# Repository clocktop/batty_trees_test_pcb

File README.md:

# batty_trees_test_pcb
KiCAD project for testing the Batty Trees TSMC June 2020 Tapeout

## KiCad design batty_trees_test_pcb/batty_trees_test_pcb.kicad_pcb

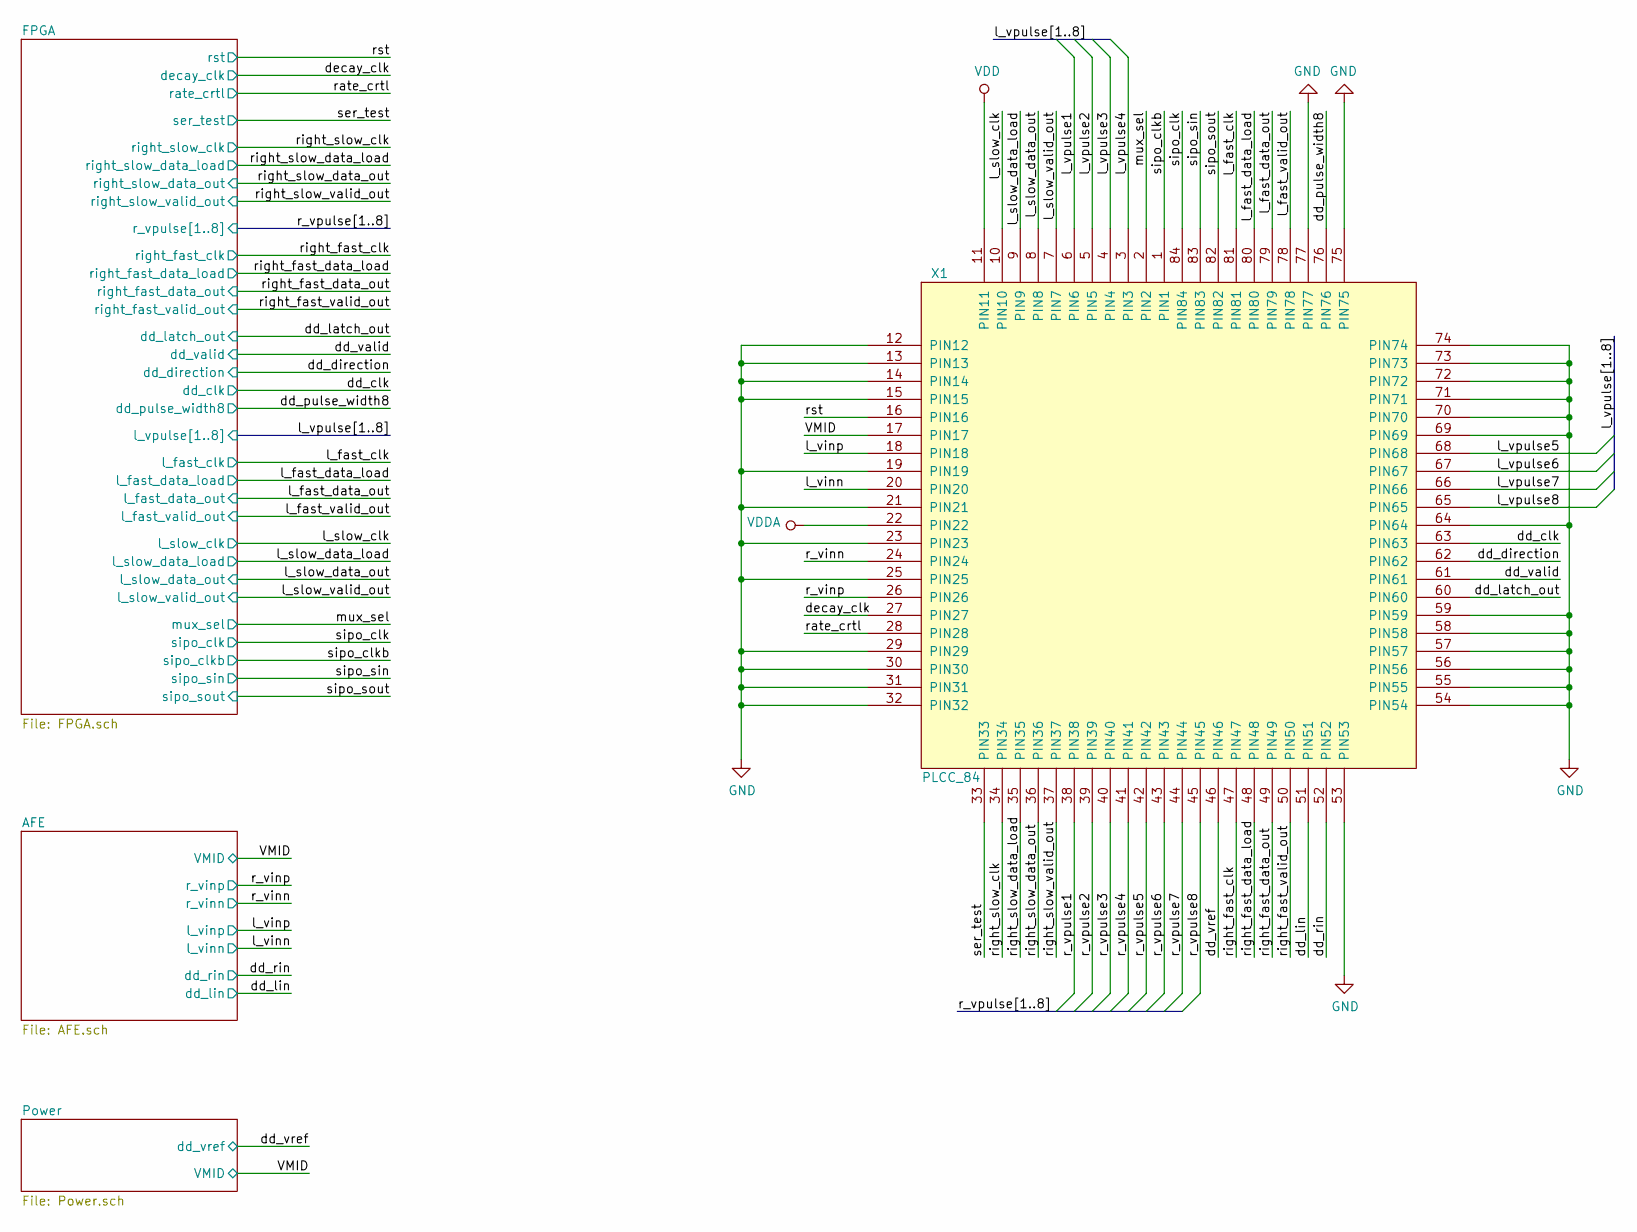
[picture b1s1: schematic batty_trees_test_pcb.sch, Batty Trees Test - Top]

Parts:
X1: PLCC_84; PLCC_84POS

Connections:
/VMID: X1.17 (PIN17); also elsewhere on the board
/dd_clk: X1.63 (PIN63); also elsewhere on the board
/dd_direction: X1.62 (PIN62); also elsewhere on the board
/dd_latch_out: X1.60 (PIN60); also elsewhere on the board
/dd_lin: X1.51 (PIN51); also elsewhere on the board
/dd_pulse_width8: X1.76 (PIN76); also elsewhere on the board
/dd_rin: X1.52 (PIN52); also elsewhere on the board
/dd_valid: X1.61 (PIN61); also elsewhere on the board
/dd_vref: X1.46 (PIN46); also elsewhere on the board
/decay_clk: X1.27 (PIN27); also elsewhere on the board
/l_fast_clk: X1.81 (PIN81); also elsewhere on the board
/l_fast_data_load: X1.80 (PIN80); also elsewhere on the board
/l_fast_data_out: X1.79 (PIN79); also elsewhere on the board
/l_fast_valid_out: X1.78 (PIN78); also elsewhere on the board
/l_slow_clk: X1.10 (PIN10); also elsewhere on the board
/l_slow_data_load: X1.9 (PIN9); also elsewhere on the board
/l_slow_data_out: X1.8 (PIN8); also elsewhere on the board
/l_slow_valid_out: X1.7 (PIN7); also elsewhere on the board
/l_vinn: X1.20 (PIN20); also elsewhere on the board
/l_vinp: X1.18 (PIN18); also elsewhere on the board
/l_vpulse1: X1.6 (PIN6); also elsewhere on the board
/l_vpulse2: X1.5 (PIN5); also elsewhere on the board
/l_vpulse3: X1.4 (PIN4); also elsewhere on the board
/l_vpulse4: X1.3 (PIN3); also elsewhere on the board
/l_vpulse5: X1.68 (PIN68); also elsewhere on the board
/l_vpulse6: X1.67 (PIN67); also elsewhere on the board
/l_vpulse7: X1.66 (PIN66); also elsewhere on the board
/l_vpulse8: X1.65 (PIN65); also elsewhere on the board
/mux_sel: X1.2 (PIN2); also elsewhere on the board
/r_vinn: X1.24 (PIN24); also elsewhere on the board
/r_vinp: X1.26 (PIN26); also elsewhere on the board
/r_vpulse1: X1.38 (PIN38); also elsewhere on the board
/r_vpulse2: X1.39 (PIN39); also elsewhere on the board
/r_vpulse3: X1.40 (PIN40); also elsewhere on the board
/r_vpulse4: X1.41 (PIN41); also elsewhere on the board
/r_vpulse5: X1.42 (PIN42); also elsewhere on the board
/r_vpulse6: X1.43 (PIN43); also elsewhere on the board
/r_vpulse7: X1.44 (PIN44); also elsewhere on the board
/r_vpulse8: X1.45 (PIN45); also elsewhere on the board
/rate_crtl: X1.28 (PIN28); also elsewhere on the board
/right_fast_clk: X1.47 (PIN47); also elsewhere on the board
/right_fast_data_load: X1.48 (PIN48); also elsewhere on the board
/right_fast_data_out: X1.49 (PIN49); also elsewhere on the board
/right_fast_valid_out: X1.50 (PIN50); also elsewhere on the board
/right_slow_clk: X1.34 (PIN34); also elsewhere on the board
/right_slow_data_load: X1.35 (PIN35); also elsewhere on the board
/right_slow_data_out: X1.36 (PIN36); also elsewhere on the board
/right_slow_valid_out: X1.37 (PIN37); also elsewhere on the board
/rst: X1.16 (PIN16); also elsewhere on the board
/ser_test: X1.33 (PIN33); also elsewhere on the board
/sipo_clk: X1.84 (PIN84); also elsewhere on the board
/sipo_clkb: X1.1 (PIN1); also elsewhere on the board
/sipo_sin: X1.83 (PIN83); also elsewhere on the board
/sipo_sout: X1.82 (PIN82); also elsewhere on the board
GND: X1.12 (PIN12), X1.13 (PIN13), X1.14 (PIN14), X1.15 (PIN15), X1.19 (PIN19), X1.21 (PIN21), X1.23 (PIN23), X1.25 (PIN25), X1.29 (PIN29), X1.30 (PIN30), X1.31 (PIN31), X1.32 (PIN32), X1.53 (PIN53), X1.54 (PIN54), X1.55 (PIN55), X1.56 (PIN56), X1.57 (PIN57), X1.58 (PIN58), X1.59 (PIN59), X1.64 (PIN64), X1.69 (PIN69), X1.70 (PIN70), X1.71 (PIN71), X1.72 (PIN72), X1.73 (PIN73), X1.74 (PIN74), X1.75 (PIN75), X1.77 (PIN77); also elsewhere on the board
VDD: X1.11 (PIN11); also elsewhere on the board
VDDA: X1.22 (PIN22); also elsewhere on the board

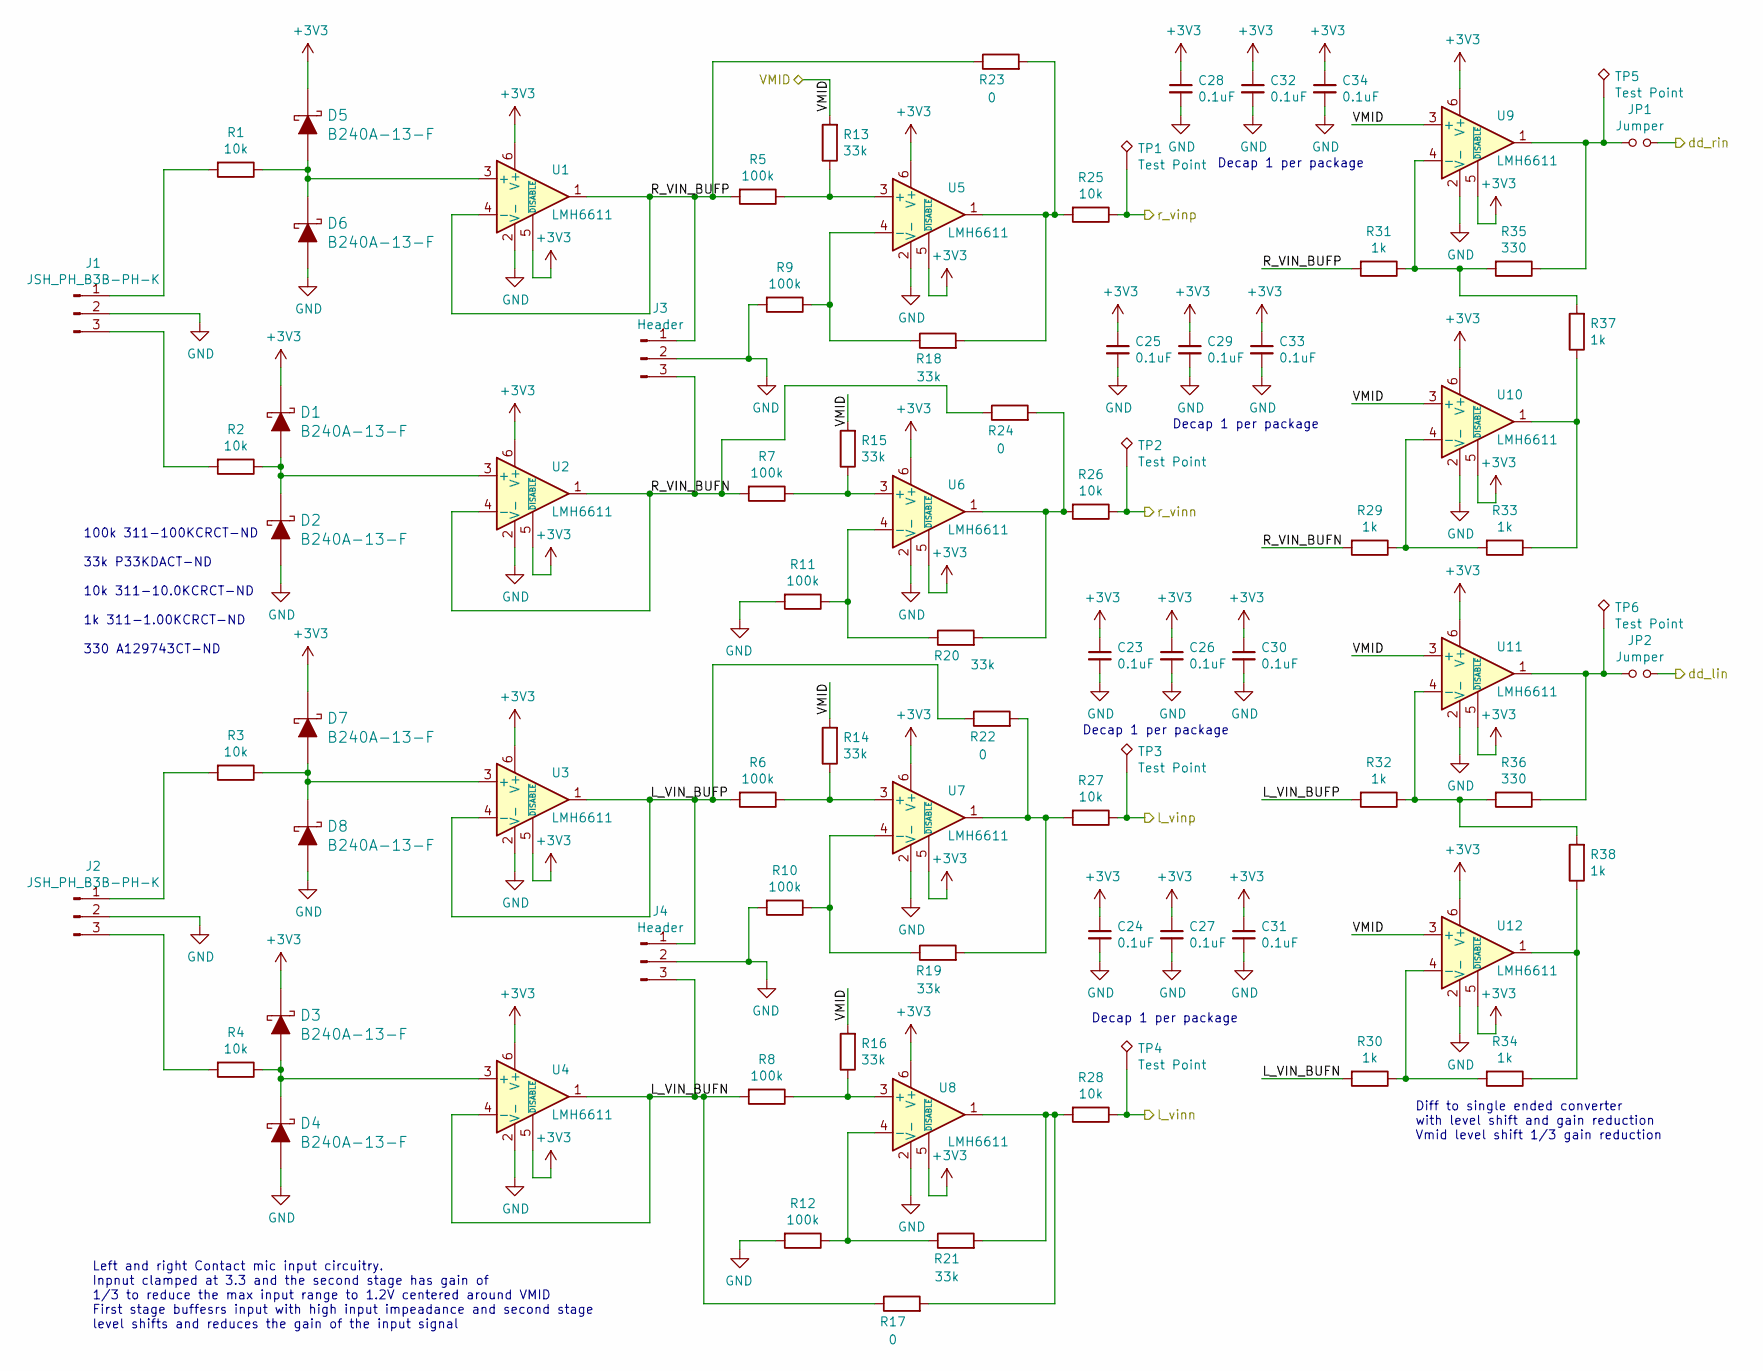
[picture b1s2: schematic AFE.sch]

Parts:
C23, C24, C25, C26, C27, C28, C29, C30, C31, C32, C33, C34: 0.1uF; C_0805_2012Metric_Pad1.15x1.40mm_HandSolder; Digi-Key_PN 399-8000-1-ND
D1, D2, D3, D4, D5, D6, D7, D8: B240A-13-F; DO-214AC; MPN B240A-13-F; Digi-Key_PN B240A-FDICT-ND
J1, J2: JSH_PH_B3B-PH-K; JST_PH_B3B-PH-K_1x03_P2.00mm_Vertical; Digi-Key_PN 455-1705-ND
J3, J4: Header; PinHeader_1x03_P2.54mm_Vertical; Digi-Key_PN 455-1705-ND
JP1, JP2: Jumper; PinHeader_1x02_P2.54mm_Vertical
R1, R2, R3, R4, R25, R26, R27, R28: 10k; R_0805_2012Metric_Pad1.15x1.40mm_HandSolder; Digi-Key_PN 311-10.0KCRCT
R5, R6, R7, R8, R9, R10, R11, R12: 100k; R_0805_2012Metric_Pad1.15x1.40mm_HandSolder; Digi-Key_PN 311-100KCRCT-ND
R13, R14, R15, R16, R18, R19, R20, R21: 33k; R_0805_2012Metric_Pad1.15x1.40mm_HandSolder; Digi-Key_PN P33KDACT-ND
R17, R22, R23, R24: 0; R_0805_2012Metric_Pad1.15x1.40mm_HandSolder
R29, R30, R31, R32, R33, R34, R37, R38: 1k; R_0805_2012Metric_Pad1.15x1.40mm_HandSolder; Digi-Key_PN 311-1.00KCRCT-ND
R35, R36: 330; R_0805_2012Metric_Pad1.15x1.40mm_HandSolder; Digi-Key_PN A129743CT-ND
TP1, TP2, TP3, TP4, TP5, TP6: Test Point; Keystone_5019; Digi-Key_PN 36-5019CT-ND
U1, U2, U3, U4, U5, U6, U7, U8, U9, U10, U11, U12: LMH6611; TSOT-23-6; Digi-Key_PN 296-41441-1-ND

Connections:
+3V3: C23.1, C24.1, C25.1, C26.1, C27.1, C28.1, C29.1, C30.1, C31.1, C32.1, C33.1, C34.1, D1.K, D3.K, D5.K, D7.K, U1.5 (~DISABLE), U1.6 (V+), U2.5 (~DISABLE), U2.6 (V+), U3.5 (~DISABLE), U3.6 (V+), U4.5 (~DISABLE), U4.6 (V+), U5.5 (~DISABLE), U5.6 (V+), U6.5 (~DISABLE), U6.6 (V+), U7.5 (~DISABLE), U7.6 (V+), U8.5 (~DISABLE), U8.6 (V+), U9.5 (~DISABLE), U9.6 (V+), U10.5 (~DISABLE), U10.6 (V+), U11.5 (~DISABLE), U11.6 (V+), U12.5 (~DISABLE), U12.6 (V+); also elsewhere on the board
/AFE/L_VIN_BUFN: J4.3, R8.2, R17.1, R30.2, U4.1, U4.4 (-)
/AFE/L_VIN_BUFP: J4.1, R6.2, R22.1, R32.2, U3.1, U3.4 (-)
/AFE/R_VIN_BUFN: J3.3, R7.2, R24.1, R29.2, U2.1, U2.4 (-)
/AFE/R_VIN_BUFP: J3.1, R5.2, R23.1, R31.2, U1.1, U1.4 (-)
/VMID: R13.2, R14.2, R15.2, R16.2, U9.3 (+), U10.3 (+), U11.3 (+), U12.3 (+); also elsewhere on the board
/dd_lin: JP2.2; also elsewhere on the board
/dd_rin: JP1.2; also elsewhere on the board
/l_vinn: R28.1, TP4.1; also elsewhere on the board
/l_vinp: R27.1, TP3.1; also elsewhere on the board
/r_vinn: R26.1, TP2.1; also elsewhere on the board
/r_vinp: R25.1, TP1.1; also elsewhere on the board
GND: C23.2, C24.2, C25.2, C26.2, C27.2, C28.2, C29.2, C30.2, C31.2, C32.2, C33.2, C34.2, D2.A, D4.A, D6.A, D8.A, J1.2, J2.2, J3.2, J4.2, R9.2, R10.2, R11.2, R12.2, U1.2 (V-), U2.2 (V-), U3.2 (V-), U4.2 (V-), U5.2 (V-), U6.2 (V-), U7.2 (V-), U8.2 (V-), U9.2 (V-), U10.2 (V-), U11.2 (V-), U12.2 (V-); also elsewhere on the board
unnamed: D1.A, D2.K, R2.1, U2.3 (+)
unnamed: D3.A, D4.K, R4.1, U4.3 (+)
unnamed: D5.A, D6.K, R1.1, U1.3 (+)
unnamed: D7.A, D8.K, R3.1, U3.3 (+)
unnamed: J1.1, R1.2
unnamed: J1.3, R2.2
unnamed: J2.1, R3.2
unnamed: J2.3, R4.2
unnamed: JP1.1, R35.1, TP5.1, U9.1
unnamed: JP2.1, R36.1, TP6.1, U11.1
unnamed: R10.1, R19.1, U7.4 (-)
unnamed: R11.1, R20.1, U6.4 (-)
unnamed: R12.1, R21.1, U8.4 (-)
unnamed: R5.1, R13.1, U5.3 (+)
unnamed: R6.1, R14.1, U7.3 (+)
unnamed: R7.1, R15.1, U6.3 (+)
unnamed: R8.1, R16.1, U8.3 (+)
unnamed: R17.2, R21.2, R28.2, U8.1
unnamed: R9.1, R18.1, U5.4 (-)
unnamed: R18.2, R23.2, R25.2, U5.1
unnamed: R19.2, R22.2, R27.2, U7.1
unnamed: R20.2, R24.2, R26.2, U6.1
unnamed: R29.1, R33.2, U10.4 (-)
unnamed: R30.1, R34.2, U12.4 (-)
unnamed: R31.1, R35.2, R37.2, U9.4 (-)
unnamed: R32.1, R36.2, R38.2, U11.4 (-)
unnamed: R33.1, R37.1, U10.1
unnamed: R34.1, R38.1, U12.1

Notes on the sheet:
Left and right Contact mic input circuitry. Inpnut clamped at 3.3 and the second stage has gain of 1/3 to reduce the max input range to 1.2V centered around VMID First stage buffesrs input with high input impeadance and second stage level shifts and reduces the gain of the input signal
Diff to single ended converter with level shift and gain reduction Vmid level shift 1/3 gain reduction
Decap 1 per package
100k 311-100KCRCT-ND 33k P33KDACT-ND 10k 311-10.0KCRCT-ND 1k 311-1.00KCRCT-ND 330 A129743CT-ND

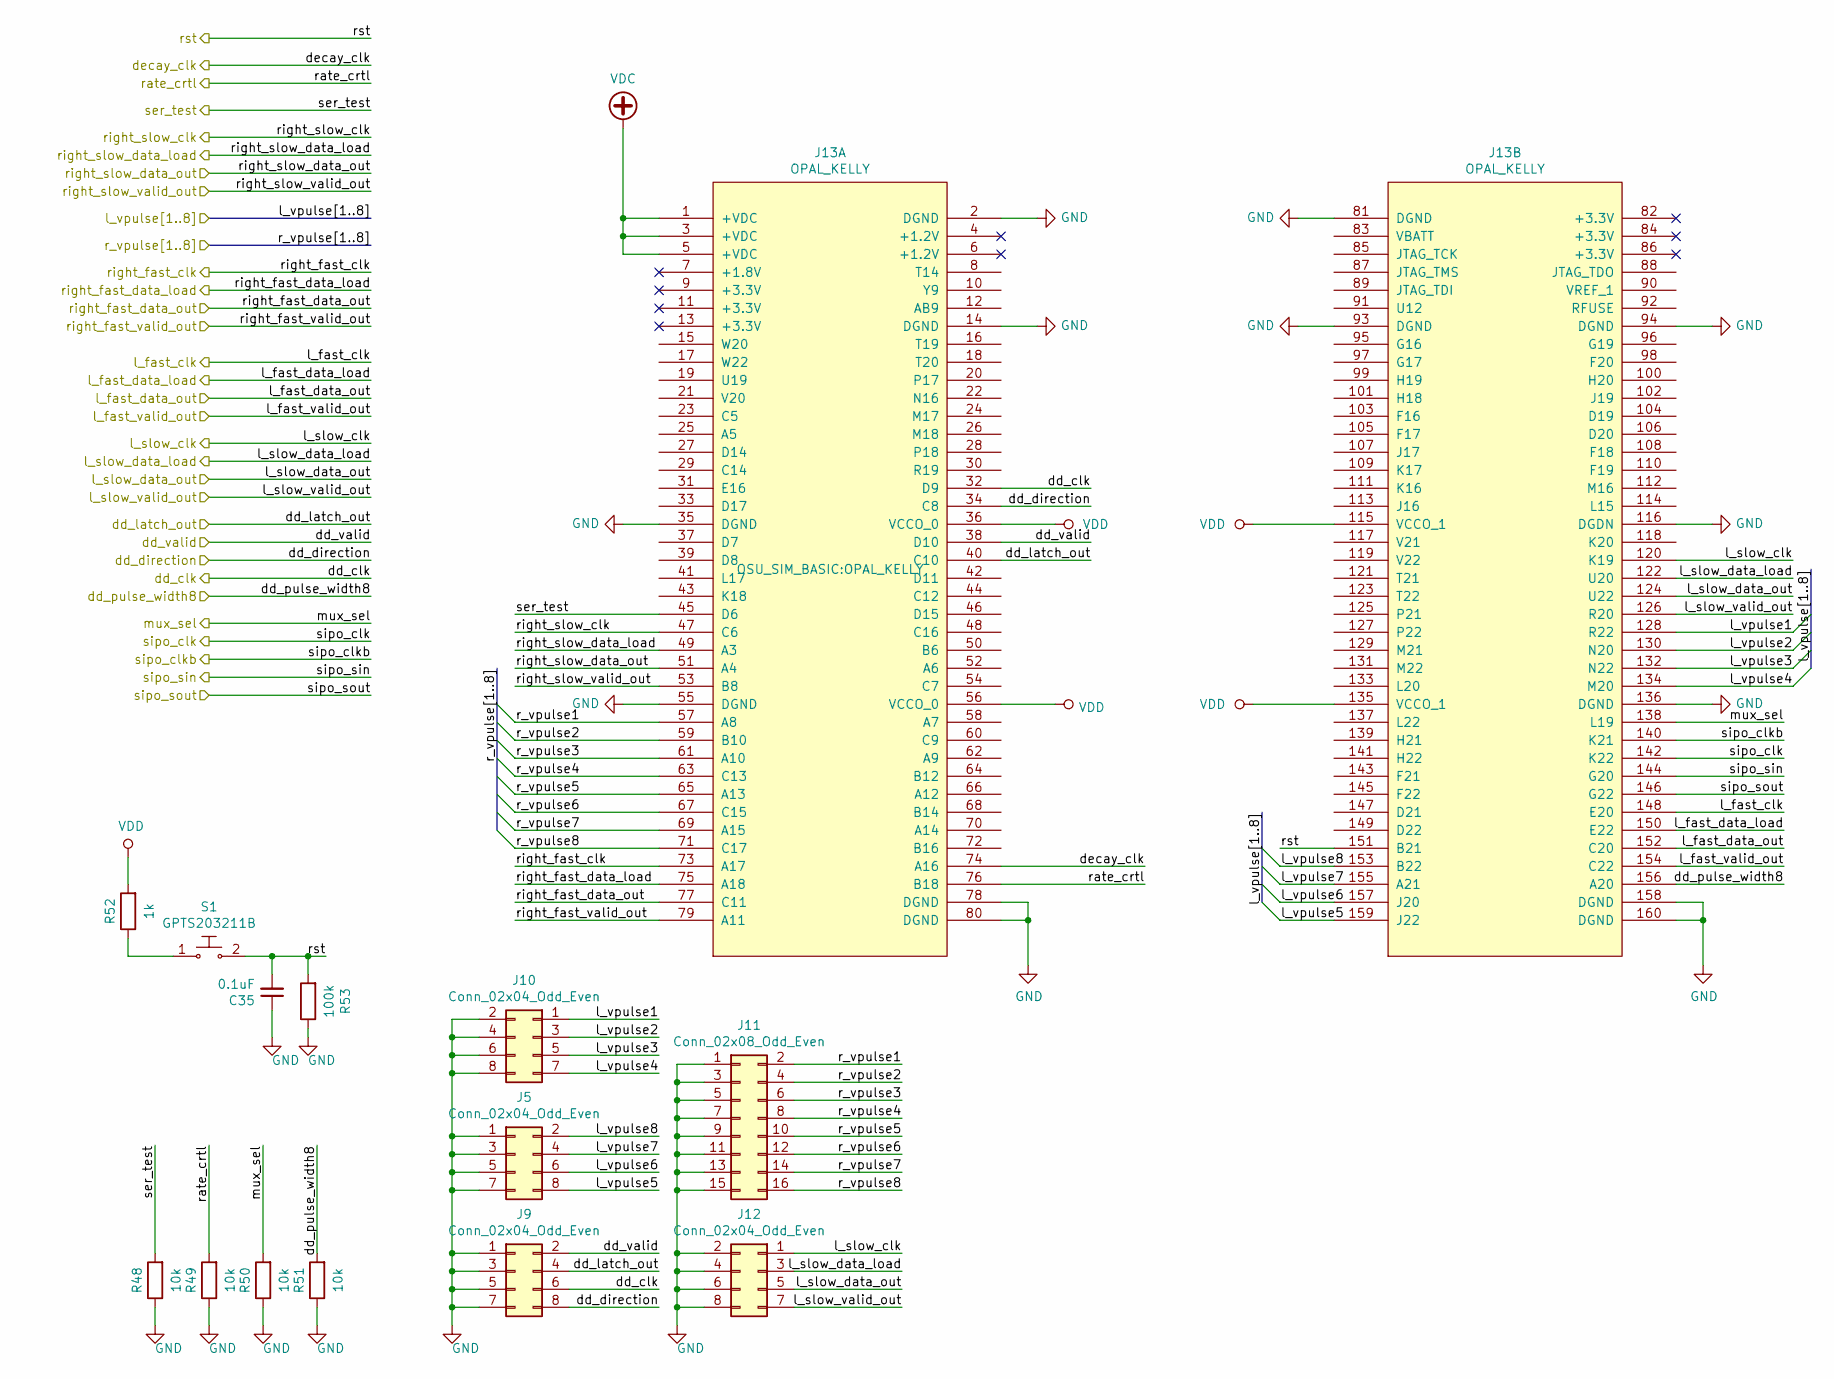
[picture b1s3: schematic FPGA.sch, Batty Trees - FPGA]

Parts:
C35: 0.1uF; C_0805_2012Metric_Pad1.15x1.40mm_HandSolder; Digi-Key_PN 399-8000-1-ND
J5, J9, J10, J12: Conn_02x04_Odd_Even; PinHeader_2x04_P2.54mm_Vertical; Digi-Key_PN 952-2122-ND
J11: Conn_02x08_Odd_Even; PinHeader_2x08_P2.54mm_Vertical; Digi-Key_PN 609-3364-ND
J13: OPAL_KELLY
R48, R49, R51: 10k; R_0805_2012Metric_Pad1.15x1.40mm_HandSolder; Digi-Key_PN 311-10.0KCRCT-ND
R50: 10k; R_0805_2012Metric_Pad1.15x1.40mm_HandSolder; Digi-Key-PN 311-10.0KCRCT-ND
R52: 1k; R_0805_2012Metric_Pad1.15x1.40mm_HandSolder; Digi-Key-PN 311-1.0KARCT-ND
R53: 100k; R_0805_2012Metric_Pad1.15x1.40mm_HandSolder; Digi-Key_PN 311-100KCRCT-ND
S1: GPTS203211B; PushButton_12x12mm_THT_GPTS203211B; MPN GPTS203211B; Digi-Key_PN CW181-ND

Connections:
/dd_clk: J9.6, J13.32 (D9); also elsewhere on the board
/dd_direction: J9.8, J13.34 (C8); also elsewhere on the board
/dd_latch_out: J9.4, J13.40 (C10); also elsewhere on the board
/dd_pulse_width8: J13.156 (A20), R51.2; also elsewhere on the board
/dd_valid: J9.2, J13.38 (D10); also elsewhere on the board
/decay_clk: J13.74 (A16); also elsewhere on the board
/l_fast_clk: J13.148 (E20); also elsewhere on the board
/l_fast_data_load: J13.150 (E22); also elsewhere on the board
/l_fast_data_out: J13.152 (C20); also elsewhere on the board
/l_fast_valid_out: J13.154 (C22); also elsewhere on the board
/l_slow_clk: J12.1, J13.120 (K19); also elsewhere on the board
/l_slow_data_load: J12.3, J13.122 (U20); also elsewhere on the board
/l_slow_data_out: J12.5, J13.124 (U22); also elsewhere on the board
/l_slow_valid_out: J12.7, J13.126 (R20); also elsewhere on the board
/l_vpulse1: J10.1, J13.128 (R22); also elsewhere on the board
/l_vpulse2: J10.3, J13.130 (N20); also elsewhere on the board
/l_vpulse3: J10.5, J13.132 (N22); also elsewhere on the board
/l_vpulse4: J10.7, J13.134 (M20); also elsewhere on the board
/l_vpulse5: J5.8, J13.159 (J22); also elsewhere on the board
/l_vpulse6: J5.6, J13.157 (J20); also elsewhere on the board
/l_vpulse7: J5.4, J13.155 (A21); also elsewhere on the board
/l_vpulse8: J5.2, J13.153 (B22); also elsewhere on the board
/mux_sel: J13.138 (L19), R50.2; also elsewhere on the board
/r_vpulse1: J11.2, J13.57 (A8); also elsewhere on the board
/r_vpulse2: J11.4, J13.59 (B10); also elsewhere on the board
/r_vpulse3: J11.6, J13.61 (A10); also elsewhere on the board
/r_vpulse4: J11.8, J13.63 (C13); also elsewhere on the board
/r_vpulse5: J11.10, J13.65 (A13); also elsewhere on the board
/r_vpulse6: J11.12, J13.67 (C15); also elsewhere on the board
/r_vpulse7: J11.14, J13.69 (A15); also elsewhere on the board
/r_vpulse8: J11.16, J13.71 (C17); also elsewhere on the board
/rate_crtl: J13.76 (B18), R49.2; also elsewhere on the board
/right_fast_clk: J13.73 (A17); also elsewhere on the board
/right_fast_data_load: J13.75 (A18); also elsewhere on the board
/right_fast_data_out: J13.77 (C11); also elsewhere on the board
/right_fast_valid_out: J13.79 (A11); also elsewhere on the board
/right_slow_clk: J13.47 (C6); also elsewhere on the board
/right_slow_data_load: J13.49 (A3); also elsewhere on the board
/right_slow_data_out: J13.51 (A4); also elsewhere on the board
/right_slow_valid_out: J13.53 (B8); also elsewhere on the board
/rst: C35.2, J13.151 (B21), R53.2, S1.2; also elsewhere on the board
/ser_test: J13.45 (D6), R48.2; also elsewhere on the board
/sipo_clk: J13.142 (K22); also elsewhere on the board
/sipo_clkb: J13.140 (K21); also elsewhere on the board
/sipo_sin: J13.144 (G20); also elsewhere on the board
/sipo_sout: J13.146 (G22); also elsewhere on the board
GND: C35.1, J5.1, J5.3, J5.5, J5.7, J9.1, J9.3, J9.5, J9.7, J10.2, J10.4, J10.6, J10.8, J11.1, J11.3, J11.5, J11.7, J11.9, J11.11, J11.13, J11.15, J12.2, J12.4, J12.6, J12.8, J13.2 (DGND), J13.14 (DGND), J13.35 (DGND), J13.55 (DGND), J13.78 (DGND), J13.80 (DGND), J13.81 (DGND), J13.93 (DGND), J13.94 (DGND), J13.116 (DGDN), J13.136 (DGND), J13.158 (DGND), J13.160 (DGND), R48.1, R49.1, R50.1, R51.1, R53.1; also elsewhere on the board
unnamed: R52.1, S1.1
VDC: J13.1 (+VDC), J13.3 (+VDC), J13.5 (+VDC); also elsewhere on the board
VDD: J13.36 (VCCO_0), J13.56 (VCCO_0), J13.115 (VCCO_1), J13.135 (VCCO_1), R52.2; also elsewhere on the board

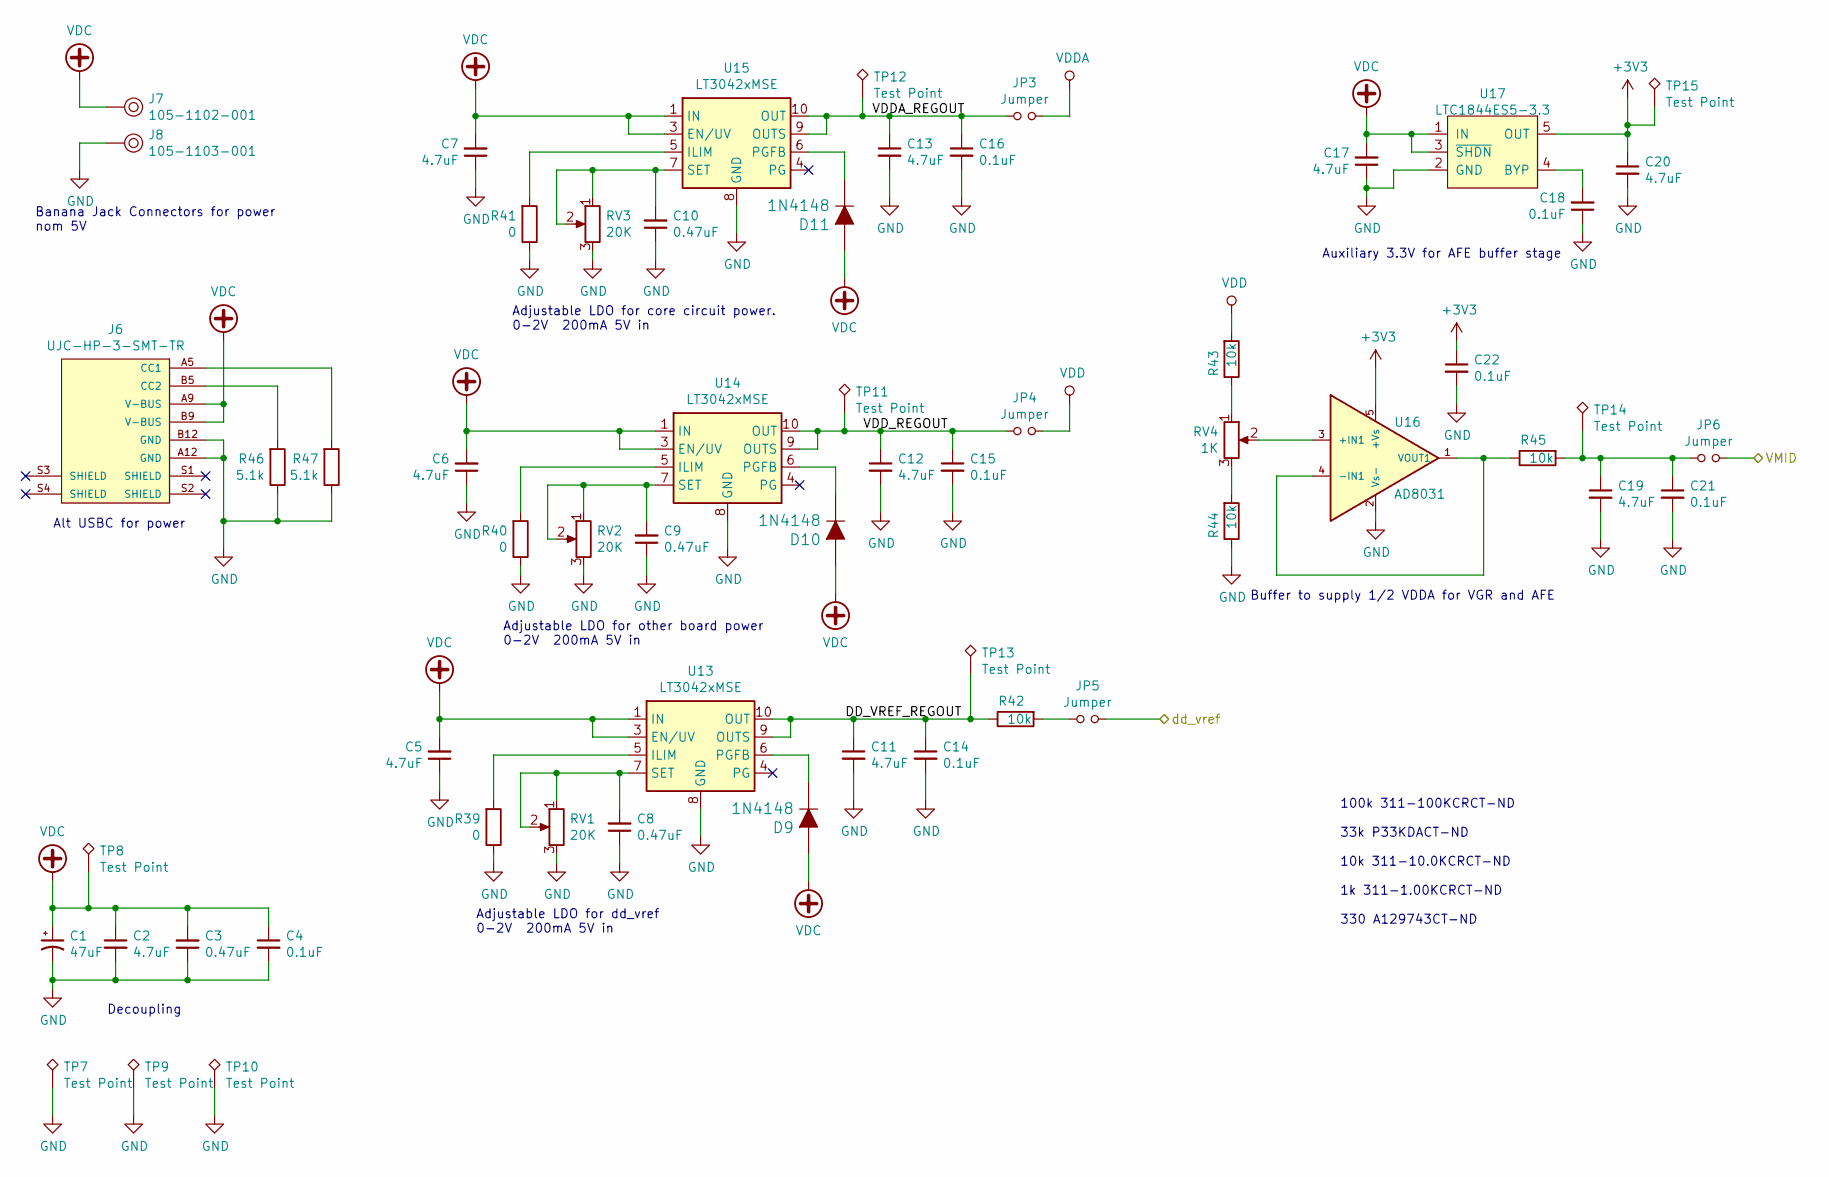
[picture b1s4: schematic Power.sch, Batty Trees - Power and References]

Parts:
C1: 47uF; CP_Elec_10x10; Digi-Key_PN EEE-FK1K470P
C2, C5, C6, C7, C11, C12, C13, C17, C19, C20: 4.7uF; C_0805_2012Metric_Pad1.15x1.40mm_HandSolder; Digi-Key_PN 490-14466-1-ND
C3, C8, C9, C10: 0.47uF; C_0805_2012Metric_Pad1.15x1.40mm_HandSolder; Digi-Key_PN 399-9247-1-ND
C4, C14, C15, C16, C18, C21, C22: 0.1uF; C_0805_2012Metric_Pad1.15x1.40mm_HandSolder; Digi-Key_PN 399-8000-1-ND
D9, D10, D11: 1N4148; SOD-123; MPN 1N4148W-7-F; Digi-Key_PN 1N4148W-FDICT-ND
J6: UJC-HP-3-SMT-TR; CUI_UJC-HP-3-SMT-TR; Digi-Key_PN 2223-UJC-HP-3-SMT-CT-ND
J7: 105-1102-001; Test_Jack_Horiz; MPN 105-1102-001; Digi-Key_PN J576-ND
J8: 105-1103-001; Test_Jack_Horiz; MPN 105-1103-001; Digi-Key_PN J577-ND
JP3, JP4, JP5, JP6: Jumper; PinHeader_1x02_P2.54mm_Vertical
R39, R40, R41: 0; C_0805_2012Metric_Pad1.15x1.40mm_HandSolder
R42, R43, R44, R45: 10k; C_0805_2012Metric_Pad1.15x1.40mm_HandSolder; Digi-Key_PN 311-10.0KCRCT-ND
R46, R47: 5.1k; C_0805_2012Metric_Pad1.15x1.40mm_HandSolder; Digi-Key_PN A126379CT-ND
RV1, RV2, RV3: 20K; Potentiometer_Bourns_3266W_Vertical; Digi-Key_PN 3266W-203LF-ND
RV4: 1K; Potentiometer_Bourns_3266W_Vertical; Digi-Key_PN 3266W-102F-ND
TP7, TP8, TP9, TP10, TP11, TP12, TP13, TP14, TP15: Test Point; Keystone_5019; Digi-Key_PN 36-5019CT-ND
U13, U14, U15: LT3042xMSE; MSOP-10-1EP_3x3mm_P0.5mm_EP1.68x1.88mm; Digi-Key_PN LT3042EMSE#TRPBFCT-ND
U16: AD8031; SOT-23-5; Digi-Key_PN AD8031ARTZ-REEL7CT-ND
U17: LTC1844ES5-3.3; SOT-23-5_HandSoldering; Digi-Key_PN LTC1844ES5-SD#TRMPBFCT-ND

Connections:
+3V3: C20.1, C22.1, TP15.1, U16.5 (+Vs), U17.5 (OUT); also elsewhere on the board
/Power/DD_VREF_REGOUT: C11.1, C14.1, R42.1, TP13.1, U13.9 (OUTS), U13.10 (OUT)
/Power/VDDA_REGOUT: C13.1, C16.1, JP3.1, TP12.1, U15.9 (OUTS), U15.10 (OUT)
/Power/VDD_REGOUT: C12.1, C15.1, JP4.1, TP11.1, U14.9 (OUTS), U14.10 (OUT)
/VMID: JP6.2; also elsewhere on the board
/dd_vref: JP5.2; also elsewhere on the board
GND: C1.2, C2.2, C3.1, C4.2, C5.1, C6.1, C7.1, C8.1, C9.1, C10.1, C11.2, C12.2, C13.2, C14.2, C15.2, C16.2, C17.1, C18.1, C19.2, C20.2, C21.2, C22.2, J6.A12 (GND), J6.B12 (GND), J8.1, R39.1, R40.1, R41.1, R44.1, R46.1, R47.1, RV1.3, RV2.3, RV3.3, TP7.1, TP9.1, TP10.1, U13.8 (GND), U13.11 (GND), U14.8 (GND), U14.11 (GND), U15.8 (GND), U15.11 (GND), U16.2 (Vs-), U17.2 (GND); also elsewhere on the board
unnamed: C8.2, RV1.1, RV1.2, U13.7 (SET)
unnamed: C9.2, RV2.1, RV2.2, U14.7 (SET)
unnamed: C10.2, RV3.1, RV3.2, U15.7 (SET)
unnamed: C18.2, U17.4 (BYP)
unnamed: C19.1, C21.1, JP6.1, R45.2, TP14.1
unnamed: D9.K, U13.6 (PGFB)
unnamed: D10.K, U14.6 (PGFB)
unnamed: D11.K, U15.6 (PGFB)
unnamed: J6.A5 (CC1), R47.2
unnamed: J6.B5 (CC2), R46.2
unnamed: JP5.1, R42.2
unnamed: R39.2, U13.5 (ILIM)
unnamed: R40.2, U14.5 (ILIM)
unnamed: R41.2, U15.5 (ILIM)
unnamed: R43.1, RV4.1
unnamed: R44.2, RV4.3
unnamed: R45.1, U16.1 (VOUT1), U16.4 (-IN1)
unnamed: RV4.2, U16.3 (+IN1)
VDC: C1.1, C2.1, C3.2, C4.1, C5.2, C6.2, C7.2, C17.2, D9.A, D10.A, D11.A, J6.A9 (V-BUS), J6.B9 (V-BUS), J7.1, TP8.1, U13.1 (IN), U13.2 (IN), U13.3 (EN/UV), U14.1 (IN), U14.2 (IN), U14.3 (EN/UV), U15.1 (IN), U15.2 (IN), U15.3 (EN/UV), U17.1 (IN), U17.3 (~SHDN); also elsewhere on the board
VDD: JP4.2, R43.2; also elsewhere on the board
VDDA: JP3.2; also elsewhere on the board

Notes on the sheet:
Banana Jack Connectors for power nom 5V
Adjustable LDO for core circuit power. 0-2V 200mA 5V in
Adjustable LDO for other board power 0-2V 200mA 5V in
Auxiliary 3.3V for AFE buffer stage
Decoupling
Adjustable LDO for dd_vref 0-2V 200mA 5V in
Buffer to supply 1/2 VDDA for VGR and AFE
Alt USBC for power
100k 311-100KCRCT-ND 33k P33KDACT-ND 10k 311-10.0KCRCT-ND 1k 311-1.00KCRCT-ND 330 A129743CT-ND
